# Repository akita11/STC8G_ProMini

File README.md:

# ST8G_ProMini

中国[STCmicro(宏晶科技)](https://www.stcmicro.com/)の8ビットマイコンSTC8G2K322を使った、Arduino Pro Mini型のマイコンボードです。
主な特徴は以下のとおりです。

- Arduino Pro Mini型（プログラム書き込みは、FTDI-Basicまたはその互換のUSB-シリアル変換器が必要です→[例](https://www.switch-science.com/catalog/1032/)）
- 電源電圧5V
- 全ピンアナログ入力・PWM出力可能
- RAM=2KB, フラッシュ=32KB
- 通信機能: UARTx4、SPI、I2C

またArduino Pro Miniとは、以下のような違いがあります。
- 現時点ではArduinoIDEでのプログラム開発環境はありませんが、[それを実現する進行中のプロジェクト](https://github.com/akita11/nulllab_stc51duino)があります。
- RAW端子に、外部電源から+7V以上を供給可能で、ボード上のレギュレータで+5Vを生成します。

## ピン配置

ボード上のArduino Pro Miniのピン位置とSTC8G2K32のピン名称との対応は以下の通りです。

- D0 - D7 : P3.0 - P3.7
- D8 - D13 : P2.0 - P2.5
- A0 - A7 : P1.0 - P1.7

基板上の"LED"（オレンジ）はP2.5（D13の位置）で駆動できます。詳細は[回路図](https://github.com/akita11/STC8G_ProMini/blob/main/STC8G_ProMini_sch.pdf)を参照してください。

## プログラムのコンパイルと書き込み

現時点では、ArduinoIDEは使えませんので、プログラムのコンパイルと書き込みは、それぞれ別のツールを使うことになります。（[使い方のメモ](https://note.com/akita11/n/n41316faaaf19)も参照してください）

### プログラムのコンパイル

STC8Gマイコンは8051コアですので、フリーから商用のものまでいろいろなコンパイラがあります。動作確認をしたものを照会しておきます。またsourceフォルダ以下に、プログラム例があります（ビルド方法は、以下のKsylitoliの手順を参照）。

- SDCC（オープンソースなコンパイラ）。Macでの使用例は[Ksylitoli](https://github.com/creeper0723/Ksylitoli)の説明がわかりやすいです。またWindows用やLinux用もあります（SDCC公式サイトからダウンロードできる）
- [FwLib_STC8](https://note.com/akita11/n/n41316faaaf19)。簡易ライブラリですが、レジスタ定義ファイルを流用できます。

### プログラムの書き込み

[STCmicro](https://www.stcmicro.com/rjxz.html)のWebページから、書き込みツールSTC-ISPをダウロードします。

USB-シリアル変換器をPCに接続し（初回時は、ここではまだSTC8G_ProMiniは接続しない）、STC-ISPを起動し、以下の設定をします。
- "MCU Type"で、**STC8G2K32S4**を選択
- "Scan Port"には、接続しているUSB-シリアル変換器のCOMポートを選択
- "Open Code File"で、コンパイルで得られた*.binを指定
- "H/W Option"で、**RESET pin used as I/O port**のチェックを**はずす**（これのチェックが入っていると、RSTピンが通常のI/Oピン(P5.4)となり、リセットSWやFTDI-Basicからのリセットがかけられません。それでもよいのでP5.4を通常のI/Oとして使用する場合はチェックを入れる）
- 内部フラッシュ内のキャリブレーション情報を使う場合は、**Add a reset code in front of ID**をチェックする

設定が済んだら、"Download/Program"ボタンを押します。

初回時のみ、その後で、FTDI-BasicにSTC8G_ProMiniを、向きに注意して接続します。（FTDI-BasicのGNDと、STC8G_ProMiniの"BLK"が揃う向き）すぐに書き込みが始まります。終了したらRSTスイッチでリセットするとプログラムが実行されます。
STC-ISPの設定で、RSTピンを使うように指定してあれば、2回目以降は、FTDI-Basicに接続したままで、Download/Promramを押すだけで自動でリセットがかかり、書き込みができます。

## Author

Junichi Akita (@akita11) / akita@ifdl.jp

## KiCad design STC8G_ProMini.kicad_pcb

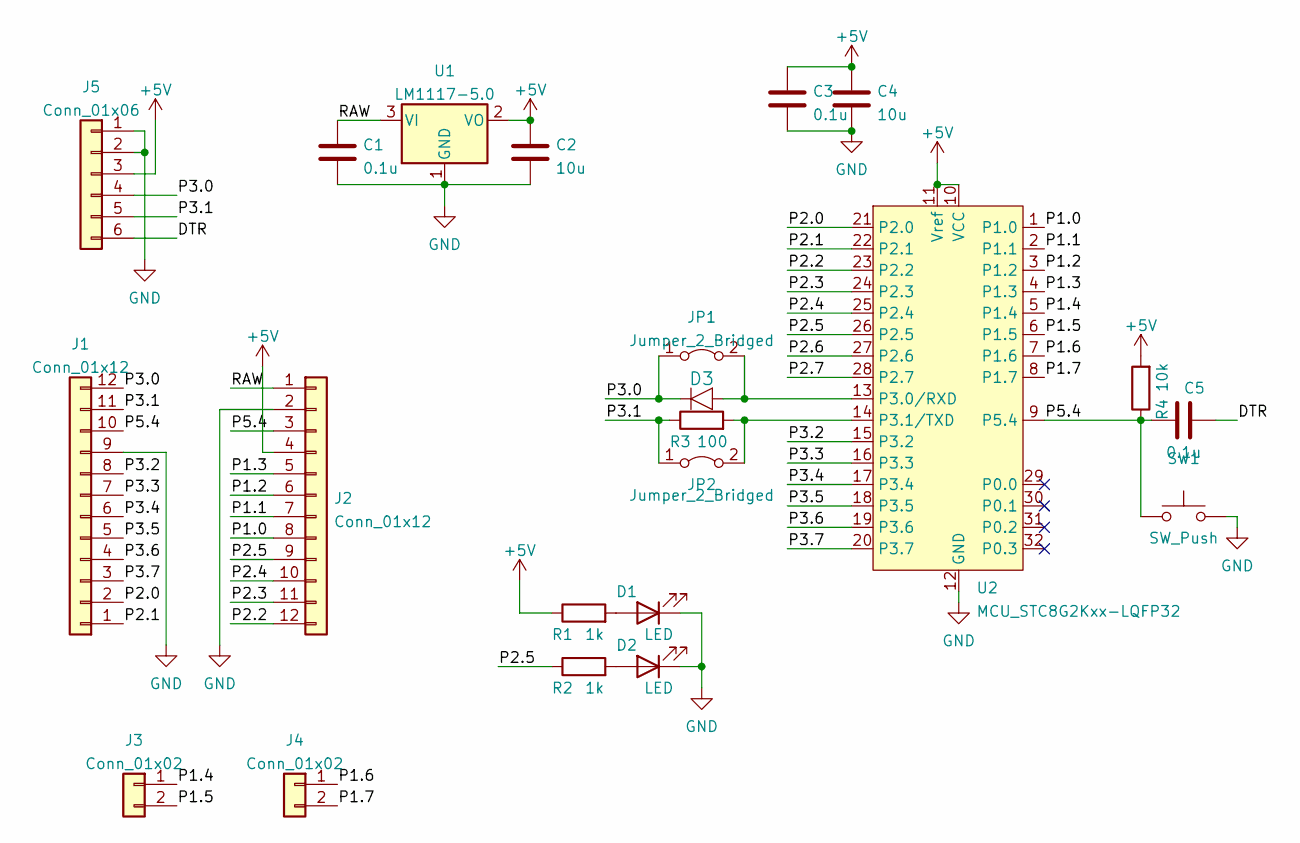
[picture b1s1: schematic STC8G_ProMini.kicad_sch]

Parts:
C1, C3, C5: 0.1u; C_0603_1608Metric
C2, C4: 10u; C_0603_1608Metric
D1, D2: LED; LED_0603_1608Metric
D3: DIODE; D_SOD123FL
J1, J2: Conn_01x12; PinSocket_1x12_P2.54mm_Vertical
J3, J4: Conn_01x02; PinSocket_1x02_P2.54mm_Vertical
J5: Conn_01x06; PinSocket_1x06_P2.54mm_Vertical
JP1, JP2: Jumper_2_Bridged; SolderJumper-2_P1.3mm_Bridged_Pad1.0x1.5mm
R1, R2: 1k; R_0603_1608Metric
R3: 100; R_0603_1608Metric
R4: 10k; R_0603_1608Metric
SW1: SW_Push; SW_Push_SPST_NO_Alps_SKRK
U1: LM1117-5.0; SOT-223-3_TabPin2
U2: MCU_STC8G2Kxx-LQFP32; LQFP-32_7x7mm_P0.8mm

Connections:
+5V: C2.1, C3.1, C4.1, J2.4, J5.3, R1.1, R4.2, U1.2 (VO), U2.10 (VCC), U2.11 (Vref)
/DTR: C5.2, J5.6
/P1.0: J2.8, U2.1 (P1.0)
/P1.1: J2.7, U2.2 (P1.1)
/P1.2: J2.6, U2.3 (P1.2)
/P1.3: J2.5, U2.4 (P1.3)
/P1.4: J3.1, U2.5 (P1.4)
/P1.5: J3.2, U2.6 (P1.5)
/P1.6: J4.1, U2.7 (P1.6)
/P1.7: J4.2, U2.8 (P1.7)
/P2.0: J1.2, U2.21 (P2.0)
/P2.1: J1.1, U2.22 (P2.1)
/P2.2: J2.12, U2.23 (P2.2)
/P2.3: J2.11, U2.24 (P2.3)
/P2.4: J2.10, U2.25 (P2.4)
/P2.5: J2.9, R2.1, U2.26 (P2.5)
/P2.6: U2.27 (P2.6)
/P2.7: U2.28 (P2.7)
/P3.0: D3.K, J1.12, J5.4, JP1.1 (A)
/P3.1: J1.11, J5.5, JP2.1 (A), R3.1
/P3.2: J1.8, U2.15 (P3.2)
/P3.3: J1.7, U2.16 (P3.3)
/P3.4: J1.6, U2.17 (P3.4)
/P3.5: J1.5, U2.18 (P3.5)
/P3.6: J1.4, U2.19 (P3.6)
/P3.7: J1.3, U2.20 (P3.7)
/P5.4: C5.1, J1.10, J2.3, R4.1, SW1.1, U2.9 (P5.4)
/RAW: C1.1, J2.1, U1.3 (VI)
GND: C1.2, C2.2, C3.2, C4.2, D1.1 (K), D2.1 (K), J1.9, J2.2, J5.1, J5.2, SW1.2, U1.1 (GND), U2.12 (GND)
unnamed: D1.2 (A), R1.2
unnamed: D2.2 (A), R2.2
unnamed: D3.A, JP1.2 (B), U2.13 (P3.0/RXD)
unnamed: JP2.2 (B), R3.2, U2.14 (P3.1/TXD)

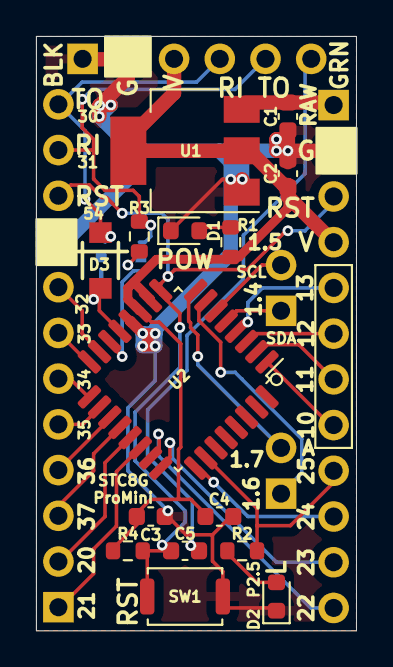
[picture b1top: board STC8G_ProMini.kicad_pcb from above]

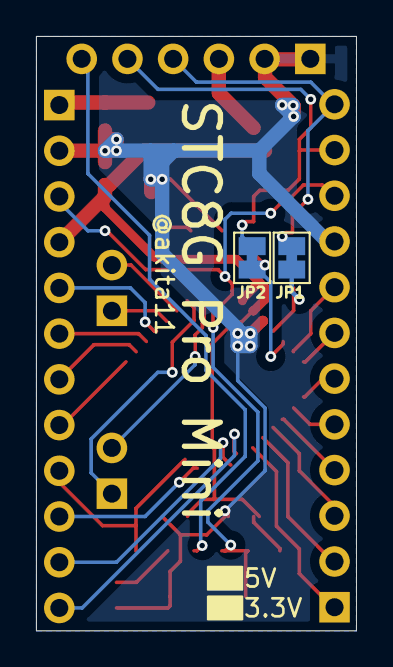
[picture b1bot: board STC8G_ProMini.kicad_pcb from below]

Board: 2 copper layers, 17.8 x 33.0 mm, 22 parts (2 on the bottom side), 31 nets.

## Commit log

2022-06-24 add connection.jpg
2025-03-21 Update README.md to correct STCmicro's URL
